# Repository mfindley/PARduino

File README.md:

PARduino
========

PARduino measures and logs photosynthetically active radiation (PAR). 
It was designed for the Barnard Ecohydology Lab at the University of Colorado, Boulder  (http://instaar.colorado.edu/research/labs-groups/ecohydrology-laboratory/).

Introduction
------------
PAR is measured during environmental monitoring and research.  We developed PARduino because it has the potential to collect environmental data in research plots at a lower cost than what we currently use for data acquisition.

Design Files
------------
PARduino is shared with the community as open source hardware (OSHW).  We hope others find it useful and will extend, modify, and otherwise improve the design.  With that in mind, this GitHub repository contains design files associated with the PARduino:
 - The Arduino code used to poll the sensor and store the measurement on a microSD flash card.
 - Designs for a printed circuit board connecting all the components.
 - A bill of materials listing parts and tools required to create a PARduino.

Making PARduino
---------------
- Procure components using the bill of materials.
- Wire the components together on a breadboard or mount them on the PCB.
- Modify the software for the gainfactor of the EME amplifier and the calibration factor of the Li-COR sensor (each Li-COR sensor has a different calibration factor).  This entails changing these values at the beginning of the PARduino source code.
- Set the time and date on the real time clock.
- Format the microSD flash card.
- Load the software onto the microcontroller using FDTI USB-to-Serial breakout board.

Using PARduino
--------------

There's really no on/off switch at this stage of development.  The device starts up as soon as it is powered.  Hitting the reset button on the Arduino Pro Mini will restart the firmware and append another block of initiallization text to the data file.  Harmless, but results in a cluttered data file.

Design Rationale
----------------

We selected the electronic components with an eye towards ease of assembly - everything can be soldered to the PCB using through-hole soldering techniques.  Since the device will be deployed in remote research plots that lack easy access to line power, battery life was also a consideration in the design.  This drove the decision to use the 3.3 Volt and 8 megahertz version of Sparkfun's Arduino Pro Mini.  This Arduino board uses less power than an Arduino Uno (both because of voltage and because it lacks the onboard USB to serial converter of the Uno).  It also drove the design of the microcontroller software - remaining in low power sleep mode until the device is ready to make a measurement dramatically extends field deployment times.

We use a 6 volt sealed lead acid battery because is has the amp-hours (listed as 8.2Ah) for extended field deployment, because it has a voltage that is high enough to run the EME amplifier (not to mention availability - there was a BatteriesPlus in town), and because the battery, while large by standards for cell phones and other consumer electronic devices, is still much  smaller than the 12 V sealed lead acid marine batteries that are commonly deployed at remote research plots.

License
-------
The code and other design documents for PARduino are released under the Creative Commons Attribution-ShareAlike 3.0 United States License. To view a copy of this license, visit http://creativecommons.org/licenses/by-sa/3.0/us/ or send a letter to Creative Commons, 444 Castro Street, Suite 900, Mountain View, California, 94041, USA.

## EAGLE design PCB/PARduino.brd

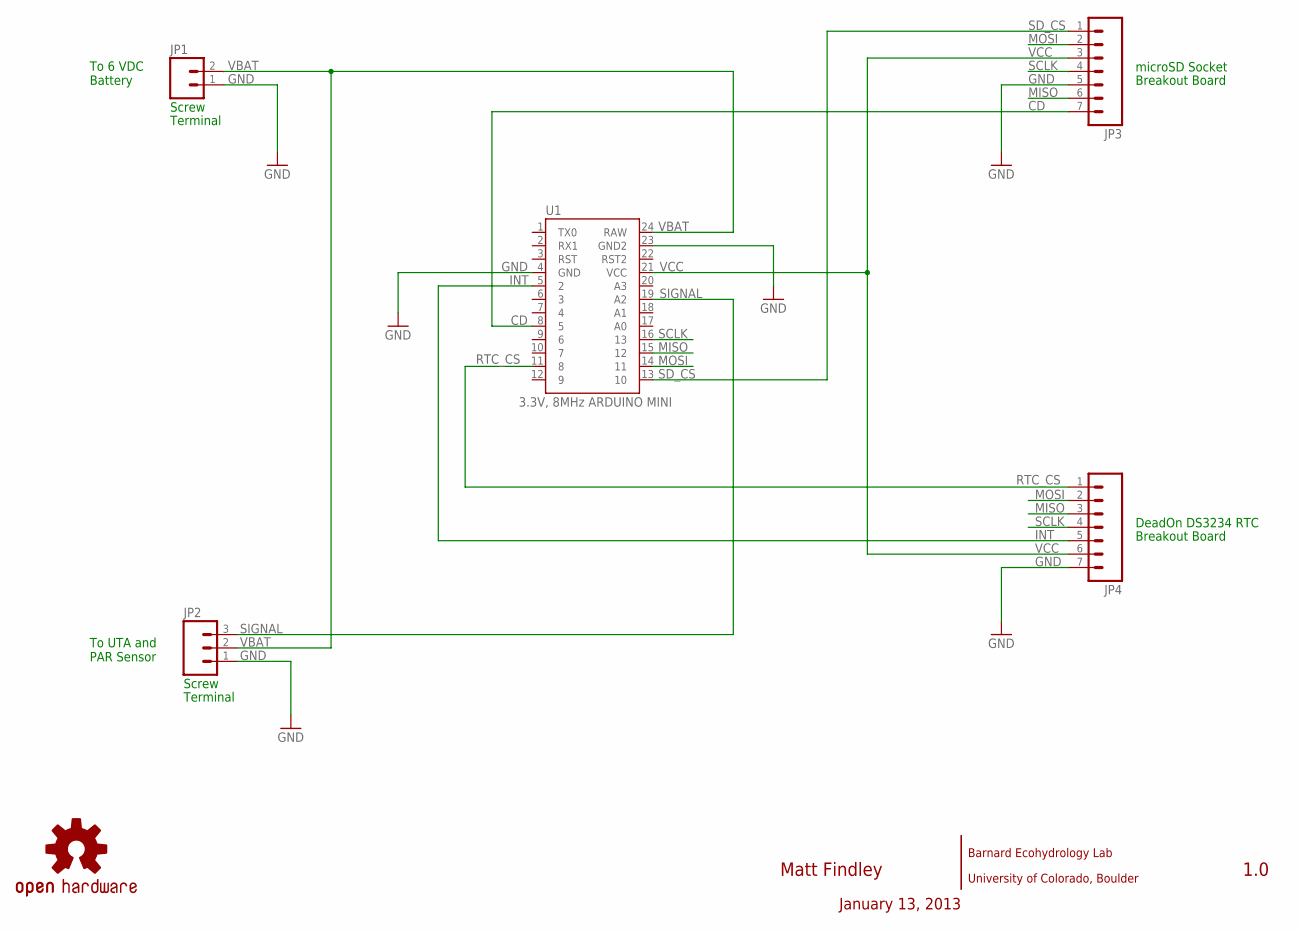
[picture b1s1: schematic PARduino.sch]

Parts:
JP1: M023.5MM_LOCK; SCREWTERMINAL-3.5MM-2_LOCK
JP2: M03SCREW; SCREWTERMINAL-3.5MM-3
JP3, JP4: M07LOCK; 1X07_LOCK
LOGO: OSHW-LOGOL; OSHW-LOGO-L
U1: 3.3V, 8MHz ARDUINO MINI; ARDUINO_MINI

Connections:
CD: JP3.7, U1.8 (5)
GND: JP1.1, JP2.1, JP3.5, JP4.7, U1.4 (GND), U1.23 (GND2)
INT: JP4.5, U1.5 (2)
MISO: JP3.6, JP4.3, U1.15 (12)
MOSI: JP3.2, JP4.2, U1.14 (11)
RTC_CS: JP4.1, U1.11 (8)
SCLK: JP3.4, JP4.4, U1.16 (13)
SD_CS: JP3.1, U1.13 (10)
SIGNAL: JP2.3, U1.19 (A2)
VBAT: JP1.2, JP2.2, U1.24 (RAW)
VCC: JP3.3, JP4.6, U1.21 (VCC)

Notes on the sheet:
To UTA and PAR Sensor
To 6 VDC Battery
Screw
Terminal
microSD Socket
Breakout Board
DeadOn DS3234 RTC
Matt Findley
Barnard Ecohydrology Lab
University of Colorado, Boulder
January 13, 2013
1.0

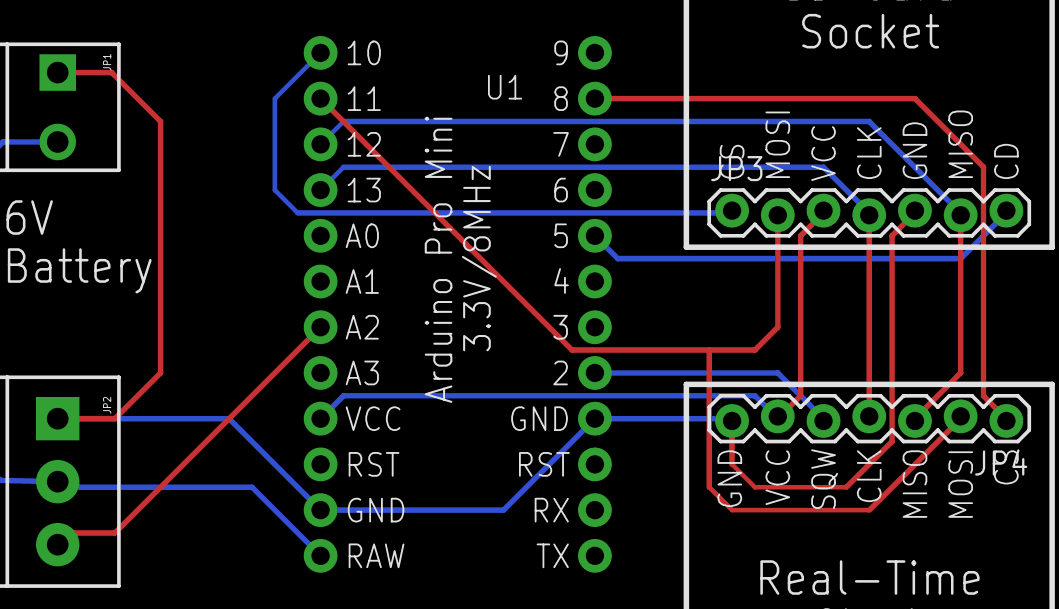
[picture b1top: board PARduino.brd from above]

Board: 2 copper layers, 10 parts (0 on the bottom side), 11 nets.

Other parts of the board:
U$1, U$2, U$3, U$4: STAND-OFF

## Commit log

2012-07-02 add sketch and notes
    add arduino sketch and random notes about the project to the repository.
2012-07-03 put sketch in folder
    Arduino IDE says that the *.ino sketch needs to be in its own folder?
    OK.
2012-07-03 separated PC and data logger serial streams
    used Arduino 1.0's SoftwareSerial library to send all the debugging info
    down the USB's serial line to the PC, but send only the final
    measurements to the OpenLog device. ... also created a "Do Nothing"
    sketch that essentially wipes the previous sketch from the
    microcontroller, so that it doesn't dump a bunch of junk to the OpenLog
    while a new sketch is being uploaded. ... not pretty, but works.
2012-07-05 real time clock functionality
    incorporated time/date stamp from a real time clock to go with the PAR
    level data. ... also added some related sketches for setting time date
    on the clock.
2012-07-07 Created Clock Read and Clock Config Sketches
    ... modified the set clock sketch and created new sketches for reading
    and writing clock time and clock config. WriteDS3234ClockConfig.ino
    looks at bit patterns of the different registers, so has a lot of zeros
    and ones.
2012-07-07 more sketch files used to figure out the clock
    ... created several arduino sketches used to figure out the
    configuration of the clock, particularly the Alarm and Interrupts.
    ... also created a version of the logging sketch that captures discrete
    measurements instead of calculating and recording average values.
2012-07-15 re-organized, created sketch w/ interrupts
    Re-organized the files to put all the intermediate sketches used to
    understand Arduino Interrupts and RTC configuration in separate folders.
    Created a version of the PAR data logging sketch that uses interrupts -
    it now logs data whenever there are 00 seconds on the clock.
2012-09-02 remove all intermediate sketches except for PARduino
    ... cleaned up the GIT directory by removing all the previous sketches
    related to this project (most were small fragments designed to better
    understand the peripherals).
    Attached the GNU GPL to the sketch.
2012-09-02 add pic
    added picture of sensor and components on a breadboard.
2012-09-02 file name change
2013-06-28 documentation updates
    changed to a creative commons license.
    documented library dependencies.
    referenced the printed circuit board.
2013-06-28 change license to creative commons.
2013-06-28 change license
    change to creative commons license.
2013-06-28 added PCB eagle files and bill of materials
2013-06-28 further tweaks to documentation.
    updated reference to the PCB now that PCB design documents have been added to the GitHub repository.
2013-06-29 starting to use github flavored markdown formatting for README file
2013-06-29 expanded ReadMe to include purpose and instructions
    work in progress.
2013-07-07 added pdf of the schematic
2013-07-07 added EME Systems amplifier manual
2013-12-01 card detect
    re-worked the code to take advantage of the card detect switch on the
    flash memory card and socket.
2014-03-09 Updated PARduino.ino to run on arduino 1.0.5 IDE
2014-03-16 80 char column width
    Reformatted for an 80 character column width
2014-03-16 Added pics and folder for pics
    added several photos of the device to the project directory and put them
    in a separated pics subdirectory.
2014-03-16 Update README.md
    Added photos. Added text about using PARduino.
2015-09-30 Fixed typographical error, changed aquisition to acquisition in README.

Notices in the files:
parts and their libraries:
SparkFun-Aesthetics: Licensing: CC v3.0 Share-Alike You are welcome to use this library for commercial purposes.
